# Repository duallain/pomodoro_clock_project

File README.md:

# pomodoro_clock_project
 A hobby electronics project

# General info

Pomodoros are a technique for trying to stay productive throught the day. You work for a bit, then take a break, alternate back and forth between those two, then take a longer break. I find it helpful to get focus during the work time, but not completely tire myself out. I couldn't find a physical clock I loved, and the 7 segment displays are so cool, I decided to try and build my own. And it seemed to turn out ok :)

# button pcb
 I ended up having quite a bit of trouble assembling a nice button layout on protoboards, so ended up buying 3 of the boards from osh park. The kicad files are all included in button_pcb, feel free to get some of your own manufactered.

# the case

There's a case for everything I modeled with onshape, link in the readme in case_model. Also included the stl. It's not the most efficent case, but it holds the display at a nice angle, gives space for the buttons to come throw, and they can be clicked, and hides all the wires and such. This will take a good minute to print, and I found the best orientation was the top (with the button holes) down against build plate, with supports for the display.

# Assembly

### solder headers to pi pico
Solder the headers to the pi pico, I went 'backwards', putting the long parts facing towards the labeled side of the pico, it makes hitting the bootsel button harder, but easier to assemble later. I soldered both rows, but didn't add the headers to the 3 debug pins on the short ends.

This article has tons of good info, and there's lots of videos showing how to do it, but essentially solder the male headers, short end through the board. https://magpi.raspberrypi.com/articles/how-to-solder-gpio-pin-headers-to-raspberry-pi-pico (I use the breadboard method and it works wonderfully.)

I highly recommend having the pin out somewhere handy, either printed out or up on a computer. https://datasheets.raspberrypi.com/pico/Pico-R3-A4-Pinout.pdf

### assemble the 7 segment display

Follow this guide, https://learn.adafruit.com/adafruit-led-backpack/1-2-inch-7-segment-backpack-assembly

You essentially put the backpack and display together, solder all the legs, then put in a 1x5 header, solder that in and you're done.

### assemble the buttons

if you have the pcb assembly is really straight forward. On the labled side you'll snap the buttons into place. There are 4 through holes per button, plus two alignment holes. Solder those in place. I found that snapping the buttons in worked great, they have plenty of strength to be flipped over and soldered. Orientation doesn't matter, they're symmetrical. You likely don't need to clip the leads, but can if you wish.
Then add the resistors. You should put these all on the non-labeled side. Solder then clip. Orientation doesn't matter here either.
Add the two headers, long side on the same side as the resistors (the 'bottom' of the pcb). the short bit should be on the same side as the buttons.

### the case

I used m2 screws everywhere, m2x12 to be exact, and washers and nuts. That worked for mounting both the button pcb and the display. I did this before continuing. You push the screw through the front, then put a washer/nut on it. Hold the nut with your finger, then turn the screw a bit. Do this for all 4 bolts, then go around again and tighten everything.  I had to hold the nuts with a pair of needle nose pliers, but if you had a tiny little 2 mm socket that'd be ideal.

### connecting things together

You can change pins if you wish, you'll just need to change the code.

You can pre make the cables, the 6 strand one is for button to pi. 5 strand is for display to pi. I'll label how many of the headers to use in each connection, but it's asymmetric, so be careful here. This is basically to save us from having to make a 2nd pcb to group pi pins together like we need.

Make all of these connections:

button pcb 1x2 header -> (with the 6 strand cable) 1 1x2 header to 2 1x1 headers -> 3.3v and gnd (GPIO 37/33). The square pad on the button pcb is the power, use a nice bright color
button pcb 1x4 header -> (with the 6 strand cable) 1 1x4 header to 1 1x4 header -> any 4 gpio in a row (gpio10-13). You may need to change pins in the code, but any 4 gpio work. To use current code, and get buttons left to right as start/stop/reset/next, connect the square pad to gpio 10.

7 seg display 1x5 header -> (with 5 strand cable) 1 1x5 header to 1x3 and 1x2 ->
1x2 header to gp 21 and 20, the scl pin on the display goes to gp21, while sda goes to gp20.
1x3 connects to vbus/vsys/ground, gound is labeled on the display, and the +5v/v_io connect to the other two pins. Doesn't really matter which, but since they're in a row there's really only one way for it to all connect.

### programming

I used arduino ide 2.x, installed the libraries called for in the code, and then plugged in the pi pico to my computer while holding the bootsel. Click upload and it should (if everything goes well) just work. The display should be on, with the time for the first pomodoro.
Click start to start counting down. Stop to stop. Reset to start from the existing timer, and next to go to the next timer. The buttons are in that order left to right while you're looking at the display.

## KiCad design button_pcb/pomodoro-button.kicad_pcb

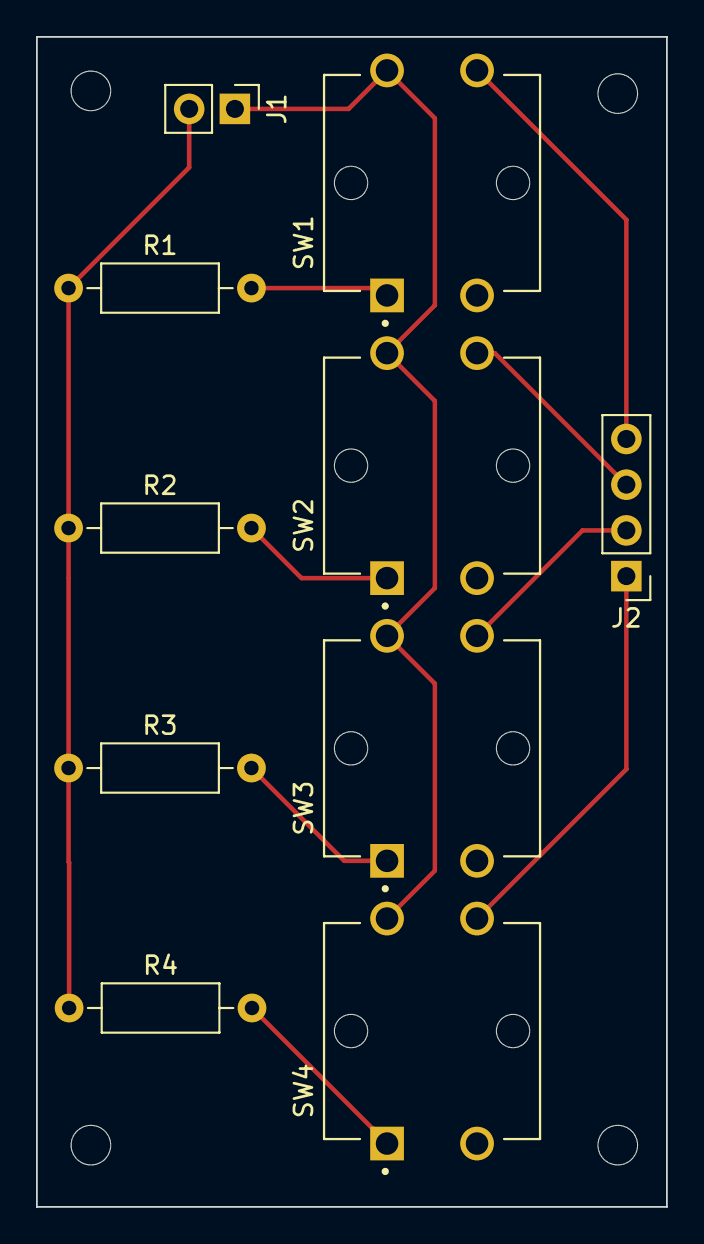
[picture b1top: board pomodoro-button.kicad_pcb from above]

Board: 2 copper layers, 35.0 x 65.0 mm, 10 parts (0 on the bottom side), 10 nets.

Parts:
J1: Conn_01x02_Male; PinHeader_1x02_P2.54mm_Vertical
J2: Conn_01x04; PinHeader_1x04_P2.54mm_Vertical
R1, R2, R3, R4: 1000; R_Axial_DIN0207_L6.3mm_D2.5mm_P10.16mm_Horizontal
SW1, SW2, SW3, SW4: SW_MEC_5E; SW_B3F-4050

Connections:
+3V3: J1.1, SW1.2, SW2.2, SW3.2, SW4.2
GND: J1.2, R1.1, R2.1, R3.1, R4.1
unnamed: J2.1, SW4.4
unnamed: J2.2, SW3.4
unnamed: J2.3, SW2.4
unnamed: J2.4, SW1.4
unnamed: R1.2, SW1.1
unnamed: R2.2, SW2.1
unnamed: R3.2, SW3.1
unnamed: R4.2, SW4.1

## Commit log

2022-08-26 Adding pcb I designed to hold the 4 buttons
2022-08-26 Initial code for the clock
2022-08-26 Case Model
2022-08-26 adding a bill of materials
2022-08-26 build info and some small updates
